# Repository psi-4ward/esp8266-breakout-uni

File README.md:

# ESP8266 Breakout Board

Simple breakout PCB für ESP8266.

* SMD Parts: 0805 handsolder
* Push-Buttons: 3x6x2,5mm

PS: If you're living in germany and need some PCBs contact me :)

### License
CC BY-NC-SA 4.0

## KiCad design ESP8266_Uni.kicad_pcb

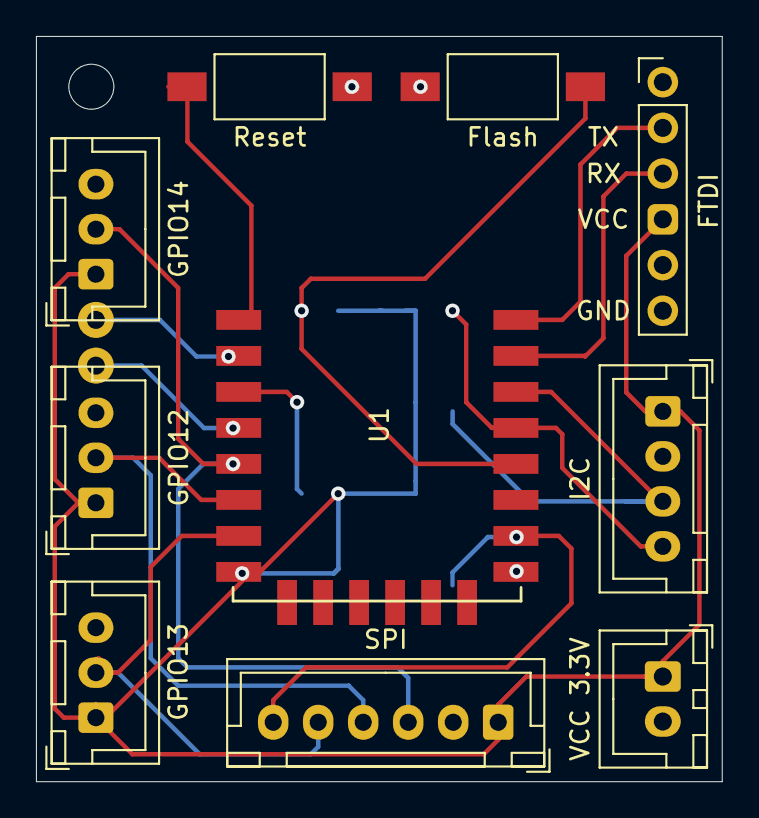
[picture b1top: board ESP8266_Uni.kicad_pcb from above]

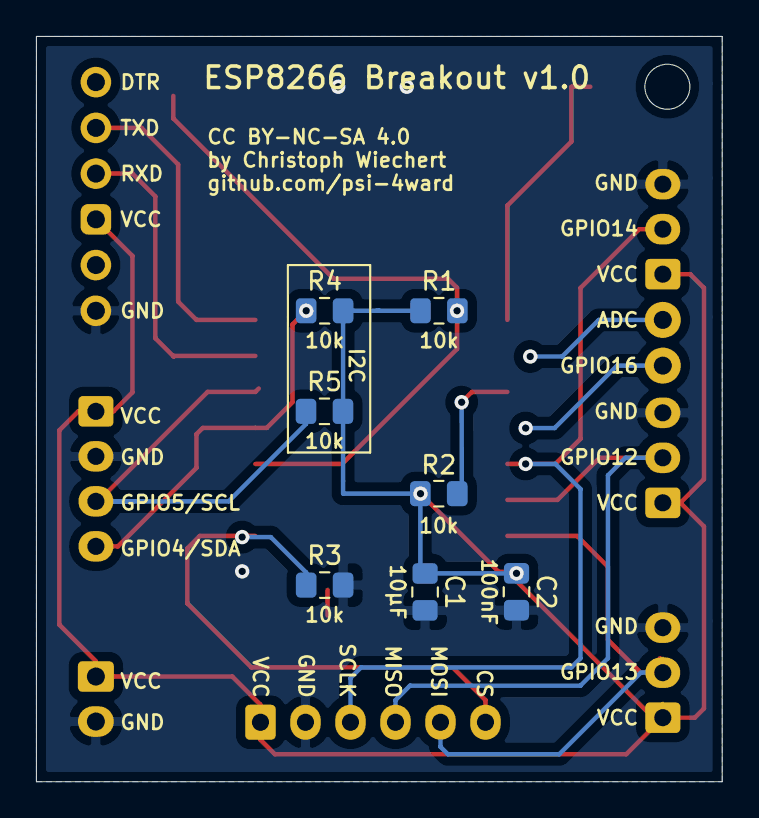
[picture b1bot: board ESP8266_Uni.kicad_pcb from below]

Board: 2 copper layers, 38.1 x 41.4 mm, 19 parts (7 on the bottom side), 15 nets.

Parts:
C1: 10µF; C_0805_2012Metric_Pad1.15x1.40mm_HandSolder
C2: 100nF; C_0805_2012Metric_Pad1.15x1.40mm_HandSolder
J1: GPIO12; JST_XH_B3B-XH-A_1x03_P2.50mm_Vertical
J2: FTDI; PinHeader_1x06_P2.54mm_Vertical
J3: GPIO13; JST_XH_B3B-XH-A_1x03_P2.50mm_Vertical
J4: VCC 3.3V; JST_XH_B2B-XH-A_1x02_P2.50mm_Vertical
J5: GPIO14; JST_XH_B3B-XH-A_1x03_P2.50mm_Vertical
J6: I2C; JST_XH_B4B-XH-A_1x04_P2.50mm_Vertical
J7: SPI; JST_XH_B6B-XH-A_1x06_P2.50mm_Vertical
J8: ADC; Pin_simple_D1.0mm_L2.0mm
J9: GPIO16; Pin_simple_D1.0mm_L2.0mm
R1, R2, R3, R4, R5: 10k; R_0805_2012Metric_Pad1.15x1.40mm_HandSolder
SW1: Reset; SW_SPST_FSMSM
SW2: Flash; SW_SPST_FSMSM
U1: ESP-12F; ESP-12E_SMD

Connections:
ADC: J8.1, U1.2
CH_PD: R2.1, U1.3
GND: C1.1, C2.1, J1.3, J2.6, J3.3, J4.2, J5.3, J6.2, J7.2, R3.2, SW1.1, SW2.1, U1.9
GPIO0: R1.2, SW2.2, U1.12
GPIO4: J6.4, R4.1, U1.13
GPIO5: J6.3, R5.1, U1.14
GPIO12: J1.2, J7.4, U1.6
GPIO13: J3.2, J7.5, U1.7
GPIO14: J5.2, J7.3, U1.5
GPIO15: J7.6, R3.1, U1.10
GPIO16: J9.1, U1.4
RESET: SW1.2, U1.1
RXD: J2.3, U1.15
TXD: J2.2, U1.16
VCC: C1.2, C2.2, J1.1, J2.4, J3.1, J4.1, J5.1, J6.1, J7.1, R1.1, R2.2, R4.2, R5.2, U1.8

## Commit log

2020-04-01 init
